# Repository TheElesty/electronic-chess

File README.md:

# electronic-chess
### Diploma thesis project

This is my implementation for electronic chess board. It uses NFC MFRC522 for pieces detection. UI consist of TFT LCD display, adressable LED and endstops/rotary encoder for input. 

This repository contains all files needed to manufacture, assemble and program electronic chessboard.

Folders contains
- [board_model](board_model/README.md) - all 3D models created in Fusion 360
- [electronic_chess](electronic_chess/README.md) - whole firmware created in Arduino IDE
- [manufacturing](manufacturing/README.md) - all files for 3D printing (prepared in Bambu studio, Anycubic Workshop and LightBurn)
- [pcb_schematics](pcb_schematics/README.md) - all schematics created in Eagle

Each directory has it own README with instructions, tutorials, etc.

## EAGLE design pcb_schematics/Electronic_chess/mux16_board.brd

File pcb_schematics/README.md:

# Eagle schematics

This folder contains all schematics used board. Either you can open schematic directli or creat new project and paste files from folder Electronic_chess inside it.

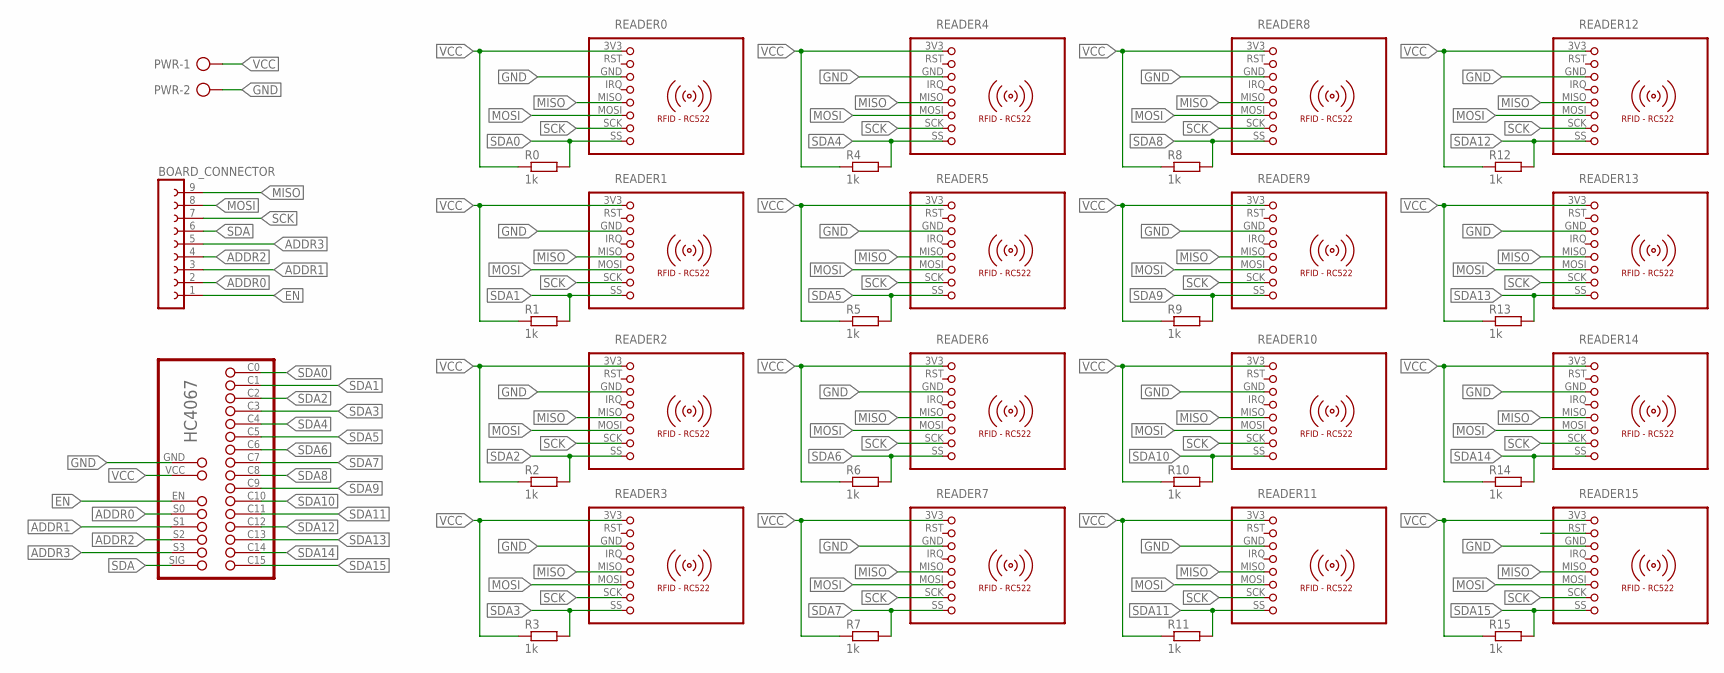
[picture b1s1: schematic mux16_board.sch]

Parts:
BOARD_CONNECTOR: FE09-1; FE09
PWR: AK500/2
R0, R1, R2, R3, R4, R5, R6, R7, R8, R9, R10, R11, R12, R13, R14, R15: 1k; 0207/10
READER0, READER1, READER2, READER3, READER4, READER5, READER6, READER7, READER8, READER9, READER10, READER11, READER12, READER13, READER14, READER15: RFID-RC522
U$1: HC4067_BREAKOUT_BOARD; ANALOG_MUX_BREAKOUT_HC4067

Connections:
ADDR0: BOARD_CONNECTOR.2, U$1.S0
ADDR1: BOARD_CONNECTOR.3, U$1.S1
ADDR2: BOARD_CONNECTOR.4, U$1.S2
ADDR3: BOARD_CONNECTOR.5, U$1.S3
EN: BOARD_CONNECTOR.1, U$1.EN
GND: PWR.2, READER0.GND (3), READER1.GND (3), READER2.GND (3), READER3.GND (3), READER4.GND (3), READER5.GND (3), READER6.GND (3), READER7.GND (3), READER8.GND (3), READER9.GND (3), READER10.GND (3), READER11.GND (3), READER12.GND (3), READER13.GND (3), READER14.GND (3), READER15.GND (3), U$1.GND
MISO: BOARD_CONNECTOR.9, READER0.MISO (5), READER1.MISO (5), READER2.MISO (5), READER3.MISO (5), READER4.MISO (5), READER5.MISO (5), READER6.MISO (5), READER7.MISO (5), READER8.MISO (5), READER9.MISO (5), READER10.MISO (5), READER11.MISO (5), READER12.MISO (5), READER13.MISO (5), READER14.MISO (5), READER15.MISO (5)
MOSI: BOARD_CONNECTOR.8, READER0.MOSI (6), READER1.MOSI (6), READER2.MOSI (6), READER3.MOSI (6), READER4.MOSI (6), READER5.MOSI (6), READER6.MOSI (6), READER7.MOSI (6), READER8.MOSI (6), READER9.MOSI (6), READER10.MOSI (6), READER11.MOSI (6), READER12.MOSI (6), READER13.MOSI (6), READER14.MOSI (6), READER15.MOSI (6)
RST: READER15.RST (2)
SCK: BOARD_CONNECTOR.7, READER0.SCK (7), READER1.SCK (7), READER2.SCK (7), READER3.SCK (7), READER4.SCK (7), READER5.SCK (7), READER6.SCK (7), READER7.SCK (7), READER8.SCK (7), READER9.SCK (7), READER10.SCK (7), READER11.SCK (7), READER12.SCK (7), READER13.SCK (7), READER14.SCK (7), READER15.SCK (7)
SDA: BOARD_CONNECTOR.6, U$1.SIG
SDA0: R0.2, READER0.SS (8), U$1.C0
SDA1: R1.2, READER1.SS (8), U$1.C1
SDA2: R2.2, READER2.SS (8), U$1.C2
SDA3: R3.2, READER3.SS (8), U$1.C3
SDA4: R4.2, READER4.SS (8), U$1.C4
SDA5: R5.2, READER5.SS (8), U$1.C5
SDA6: R6.2, READER6.SS (8), U$1.C6
SDA7: R7.2, READER7.SS (8), U$1.C7
SDA8: R8.2, READER8.SS (8), U$1.C8
SDA9: R9.2, READER9.SS (8), U$1.C9
SDA10: R10.2, READER10.SS (8), U$1.C10
SDA11: R11.2, READER11.SS (8), U$1.C11
SDA12: R12.2, READER12.SS (8), U$1.C12
SDA13: R13.2, READER13.SS (8), U$1.C13
SDA14: R14.2, READER14.SS (8), U$1.C14
SDA15: R15.2, READER15.SS (8), U$1.C15
VCC: PWR.1, R0.1, R1.1, R2.1, R3.1, R4.1, R5.1, R6.1, R7.1, R8.1, R9.1, R10.1, R11.1, R12.1, R13.1, R14.1, R15.1, READER0.3V3 (1), READER1.3V3 (1), READER2.3V3 (1), READER3.3V3 (1), READER4.3V3 (1), READER5.3V3 (1), READER6.3V3 (1), READER7.3V3 (1), READER8.3V3 (1), READER9.3V3 (1), READER10.3V3 (1), READER11.3V3 (1), READER12.3V3 (1), READER13.3V3 (1), READER14.3V3 (1), READER15.3V3 (1), U$1.VCC

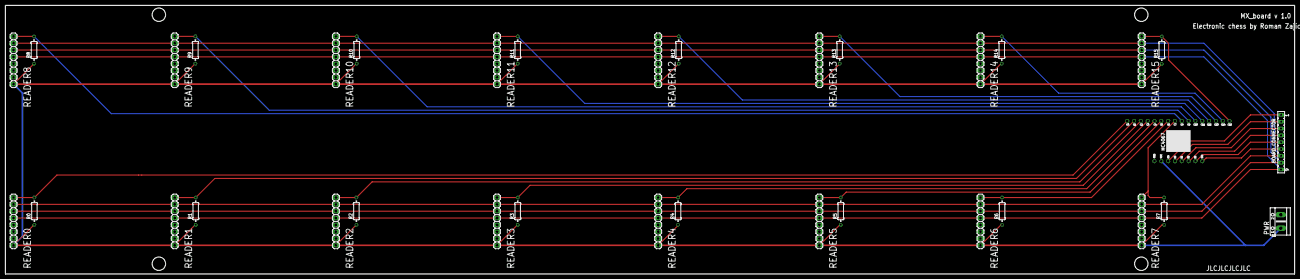
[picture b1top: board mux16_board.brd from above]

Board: 2 copper layers, 480.0 x 100.0 mm, 35 parts (0 on the bottom side), 27 nets.

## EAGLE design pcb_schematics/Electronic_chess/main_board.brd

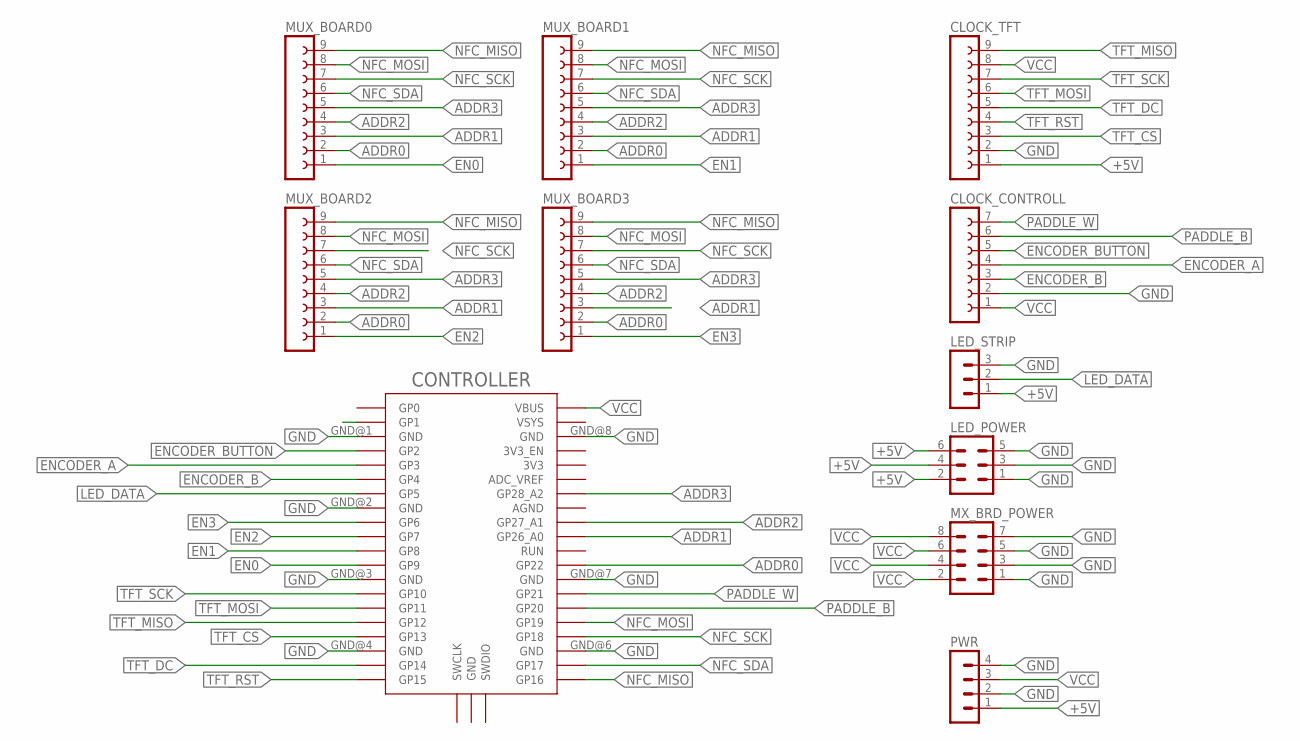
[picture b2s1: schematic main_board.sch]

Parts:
CLOCK_CONTROLL: FE07-1; FE07
CLOCK_TFT: FE09-1; FE09
CONTROLLER: RPI_PICO_IG-TH; RPI_PICO_TH
LED_POWER: MA03-2
LED_STRIP: MA03-1
MUX_BOARD0, MUX_BOARD1, MUX_BOARD2, MUX_BOARD3: FE09-1; FE09
MX_BRD_POWER: MA04-2
PWR: MA04-1

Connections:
+5V: CLOCK_TFT.1, LED_POWER.2, LED_POWER.4, LED_POWER.6, LED_STRIP.1, PWR.1
ADDR0: CONTROLLER.GP22, MUX_BOARD0.2, MUX_BOARD1.2, MUX_BOARD2.2, MUX_BOARD3.2
ADDR1: CONTROLLER.GP26_A0, MUX_BOARD0.3, MUX_BOARD1.3, MUX_BOARD2.3, MUX_BOARD3.3
ADDR2: CONTROLLER.GP27_A1, MUX_BOARD0.4, MUX_BOARD1.4, MUX_BOARD2.4, MUX_BOARD3.4
ADDR3: CONTROLLER.GP28_A2, MUX_BOARD0.5, MUX_BOARD1.5, MUX_BOARD2.5, MUX_BOARD3.5
EN0: CONTROLLER.GP9, MUX_BOARD0.1
EN1: CONTROLLER.GP8, MUX_BOARD1.1
EN2: CONTROLLER.GP7, MUX_BOARD2.1
EN3: CONTROLLER.GP6, MUX_BOARD3.1
ENCODER_A: CLOCK_CONTROLL.4, CONTROLLER.GP3
ENCODER_B: CLOCK_CONTROLL.3, CONTROLLER.GP4
ENCODER_BUTTON: CLOCK_CONTROLL.5, CONTROLLER.GP2
GND: CLOCK_CONTROLL.2, CLOCK_TFT.2, CONTROLLER.GND@1 (GND), CONTROLLER.GND@2 (GND), CONTROLLER.GND@3 (GND), CONTROLLER.GND@4 (GND), CONTROLLER.GND@6 (GND), CONTROLLER.GND@7 (GND), CONTROLLER.GND@8 (GND), LED_POWER.1, LED_POWER.3, LED_POWER.5, LED_STRIP.3, MX_BRD_POWER.1, MX_BRD_POWER.3, MX_BRD_POWER.5, MX_BRD_POWER.7, PWR.2, PWR.4
LED_DATA: CONTROLLER.GP5, LED_STRIP.2
NFC_MISO: CONTROLLER.GP16, MUX_BOARD0.9, MUX_BOARD1.9, MUX_BOARD2.9, MUX_BOARD3.9
NFC_MOSI: CONTROLLER.GP19, MUX_BOARD0.8, MUX_BOARD1.8, MUX_BOARD2.8, MUX_BOARD3.8
NFC_SCK: CONTROLLER.GP18, MUX_BOARD0.7, MUX_BOARD1.7, MUX_BOARD2.7, MUX_BOARD3.7
NFC_SDA: CONTROLLER.GP17, MUX_BOARD0.6, MUX_BOARD1.6, MUX_BOARD2.6, MUX_BOARD3.6
PADDLE_B: CLOCK_CONTROLL.6, CONTROLLER.GP20
PADDLE_W: CLOCK_CONTROLL.7, CONTROLLER.GP21
TFT_CS: CLOCK_TFT.3, CONTROLLER.GP13
TFT_DC: CLOCK_TFT.5, CONTROLLER.GP14
TFT_MISO: CLOCK_TFT.9, CONTROLLER.GP12
TFT_MOSI: CLOCK_TFT.6, CONTROLLER.GP11
TFT_RST: CLOCK_TFT.4, CONTROLLER.GP15
TFT_SCK: CLOCK_TFT.7, CONTROLLER.GP10
VCC: CLOCK_CONTROLL.1, CLOCK_TFT.8, CONTROLLER.VBUS, MX_BRD_POWER.2, MX_BRD_POWER.4, MX_BRD_POWER.6, MX_BRD_POWER.8, PWR.3

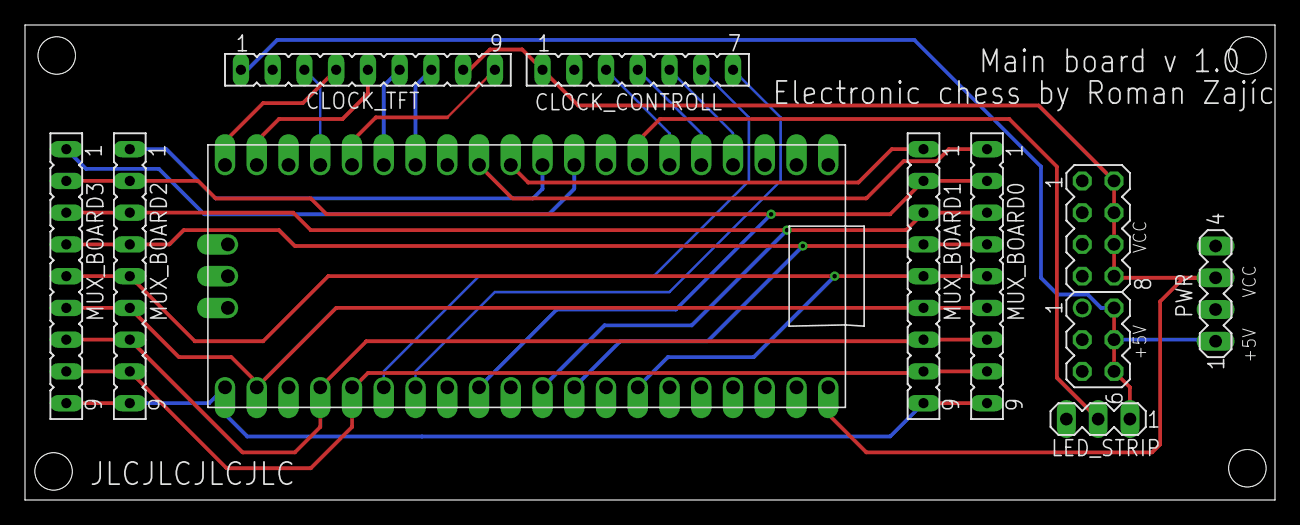
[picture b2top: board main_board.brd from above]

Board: 2 copper layers, 100.0 x 38.0 mm, 11 parts (0 on the bottom side), 27 nets.

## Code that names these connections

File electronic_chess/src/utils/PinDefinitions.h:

#pragma once

//Encoder
#define PIN_ENC_BUTTON 2
#define PIN_ENC_A 3
#define PIN_ENC_B 4

//Paddle
#define PIN_PADDLE_W 21
#define PIN_PADDLE_B 20

//Adressable leds
#define PIN_LED_DATA 5

//NFC
#define PIN_NFC_RST 0
#define PIN_NFC_SS  17

//Multiplexor
#define PIN_EN_0  9
#define PIN_EN_1  8
#define PIN_EN_2  7
#define PIN_EN_3  6

#define PIN_ADDR0 22
#define PIN_ADDR1 26
#define PIN_ADDR2 27
#define PIN_ADDR3 28

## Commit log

2024-05-08 electronich_chess init files
2024-05-08 Update README.md in pcb_
2024-05-08 Update README.md manufacturing
2024-05-08 Rename piece_set.pwscene to piece_set_2x.pwscene
2024-05-08 Rename piece_set.3mf to piece_set_2x.3mf
2024-05-08 Rename light_tunels.pwscene to light_tunels_4x.pwscene
2024-05-08 Update README.md board
2024-05-08 Update README.md firmware
